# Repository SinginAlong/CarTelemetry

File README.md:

# CarTelemetry

## Goal
Hope to use an RPi, a GPS and a IMU to accurately track a car on the road or track

## Materials
Adafruit Ultimate GPS V3 (possibly with different antenna)
Adafruit BNO055 IMU
Raspberry PI 3 (don't need the power of the 4)

## PCB Board Requirements
- PCB will mount on RPi, including using screws
- GPS and IMU will mount on top of board (may use screw holes)
- Final assembly must be securable to a surface in an enclosure box
- Board will take 12V from car, clean it (de-surge, de-dip), and regulate it to 5V
- Board will pass ignition line to RPi, with protections

## PCB Board Connections

### Car
- Power in (from battery, never shuts off)
- Ignition in (goes high when car electronics are on, low when car is shut off)
- Ground

### Ultimate GPS
- VIN (3-5VDC)
- Ground
- VBAT (3.3 power to GPS RTC) (run from car batt with long (month) timer?)
- EN (enable), ground to shut off GPS (use when ignition is lost?)
- 3.3V out (if you need 3.3 volts)
- TX 
- RX
- Fix (pulses low high when no fix, stays low for 15 seconds when fixed)
- PPS (pulse per second, for timing)

### BNO055 IMU
- VIN (3.3 to 5 V)
- 3VO (3.3 volts out from reg, 50ma available)
- GND
- SCL (i2c clock pin)
- SDA (i2c data pin)
- RST, hardware reset (low then high, 5V safe)
- INT, interrput output pin, 3V
- ADR, set high to change i2c address from 0x28 to 0x29
- PS0, PS1 (config stuff, don't connect)

### RPi
- all the pins

## TODO
- Write down vision for project
- Create requirements for board
- List limitations from environment
- Start designing board in Eagle CAD

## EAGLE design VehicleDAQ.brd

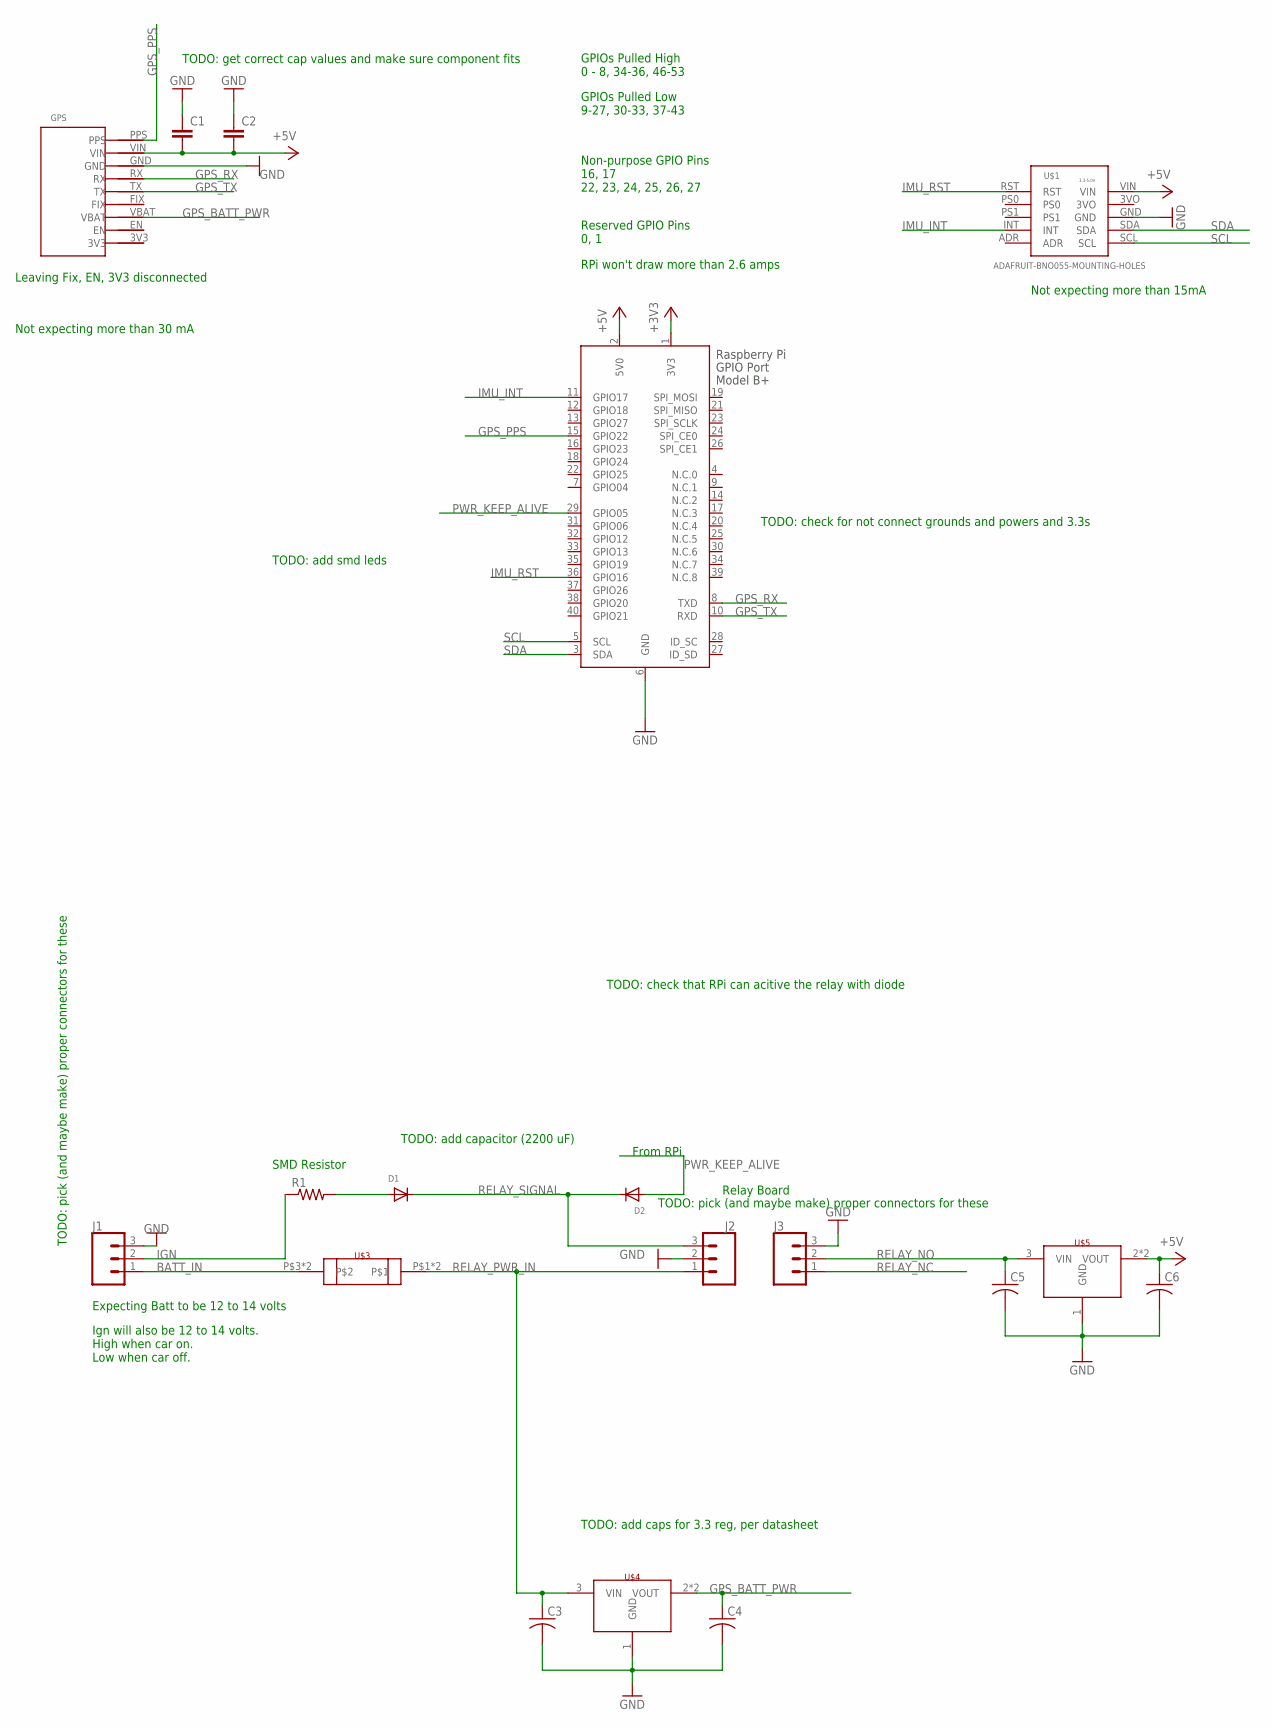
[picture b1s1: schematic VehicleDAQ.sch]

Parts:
C1, C2: C-EU025-030X050; C025-030X050
C3, C4, C5, C6: C-USC1206K; C1206K
D1, D2: DIODEDO-1N4148; DO-1N4148
J1: CONN_03SCREW_LOCK; SCREWTERMINAL-3.5MM-3_LOCK.007S
J2, J3: CONN_03; 1X03
R1: R-US_R1206W; R1206W
U$1: ADAFRUIT-BNO055-MOUNTING-HOLES
U$2: ADAFRUIT-ULTIMATE-GPS-MOUNTING-HOLES; GPS-WITH-MOUNTING-HOLES
U$3: BLADE_FUSE_BLOCK; FUSE_HOLDER
U$4, U$5: LD1085D2M33R_REGULATOR; TO263-3
X1: RASPI_BOARD_B+_FP; RASPI_BOARD_B+_FULL_PAD

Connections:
+3V3: X1.1 (3V3)
+5V: C1.2, C2.2, C6.1, U$1.VIN, U$2.VIN, U$5.2 (VOUT), U$5.TAB (VOUT), X1.2 (5V0)
BATT_IN: J1.1, U$3.P$3, U$3.P$4
GND: C1.1, C2.1, C3.2, C4.2, C5.2, C6.2, J1.3, J2.2, J3.3, U$1.GND, U$2.GND, U$4.1 (GND), U$5.1 (GND), X1.6 (GND)
GPS_BATT_PWR: C4.1, U$2.VBAT, U$4.2 (VOUT), U$4.TAB (VOUT)
GPS_PPS: U$2.PPS, X1.15 (GPIO22)
GPS_RX: U$2.RX, X1.8 (TXD)
GPS_TX: U$2.TX, X1.10 (RXD)
IGN: J1.2, R1.1
IMU_INT: U$1.INT, X1.11 (GPIO17)
IMU_RST: U$1.RST, X1.36 (GPIO16)
unnamed: D1.A, R1.2
PWR_KEEP_ALIVE: D2.A, X1.29 (GPIO05)
RELAY_NC: J3.1
RELAY_NO: C5.1, J3.2, U$5.3 (VIN)
RELAY_PWR_IN: C3.1, J2.1, U$3.P$1, U$3.P$2, U$4.3 (VIN)
RELAY_SIGNAL: D1.C, D2.C, J2.3
SCL: U$1.SCL, X1.5 (SCL)
SDA: U$1.SDA, X1.3 (SDA)

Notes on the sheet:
Non-purpose GPIO Pins 16, 17 22, 23, 24, 25, 26, 27
Reserved GPIO Pins 0, 1
GPIOs Pulled High 0 - 8, 34-36, 46-53
GPIOs Pulled Low 9-27, 30-33, 37-43
Leaving Fix, EN, 3V3 disconnected
Expecting Batt to be 12 to 14 volts
Ign will also be 12 to 14 volts. High when car on. Low when car off.
Relay Board
From RPi
SMD Resistor
TODO: add capacitor (2200 uF)
TODO: get correct cap values and make sure component fits
TODO: add smd leds
TODO: check for not connect grounds and powers and 3.3s
TODO: check that RPi can acitive the relay with diode
TODO: pick (and maybe make) proper connectors for these
RPi won't draw more than 2.6 amps
Not expecting more than 30 mA
Not expecting more than 15mA
TODO: add caps for 3.3 reg, per datasheet

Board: 2 copper layers, 18 parts (0 on the bottom side), 17 nets, no tracks yet.

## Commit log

2020-07-16 Update README.md
    Added board requirements and module input and outputs
2020-11-29 Mostly complete schematic. Need to choose many of the actual componenets still
2020-12-06 Added actual regulators and capacitors. All surface mount caps and regulators.

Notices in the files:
parts and their libraries:
SparkFun-Connectors: Licensing: Creative Commons ShareAlike 4.0 International - https://creativecommons.org/licenses/by-sa/4.0
